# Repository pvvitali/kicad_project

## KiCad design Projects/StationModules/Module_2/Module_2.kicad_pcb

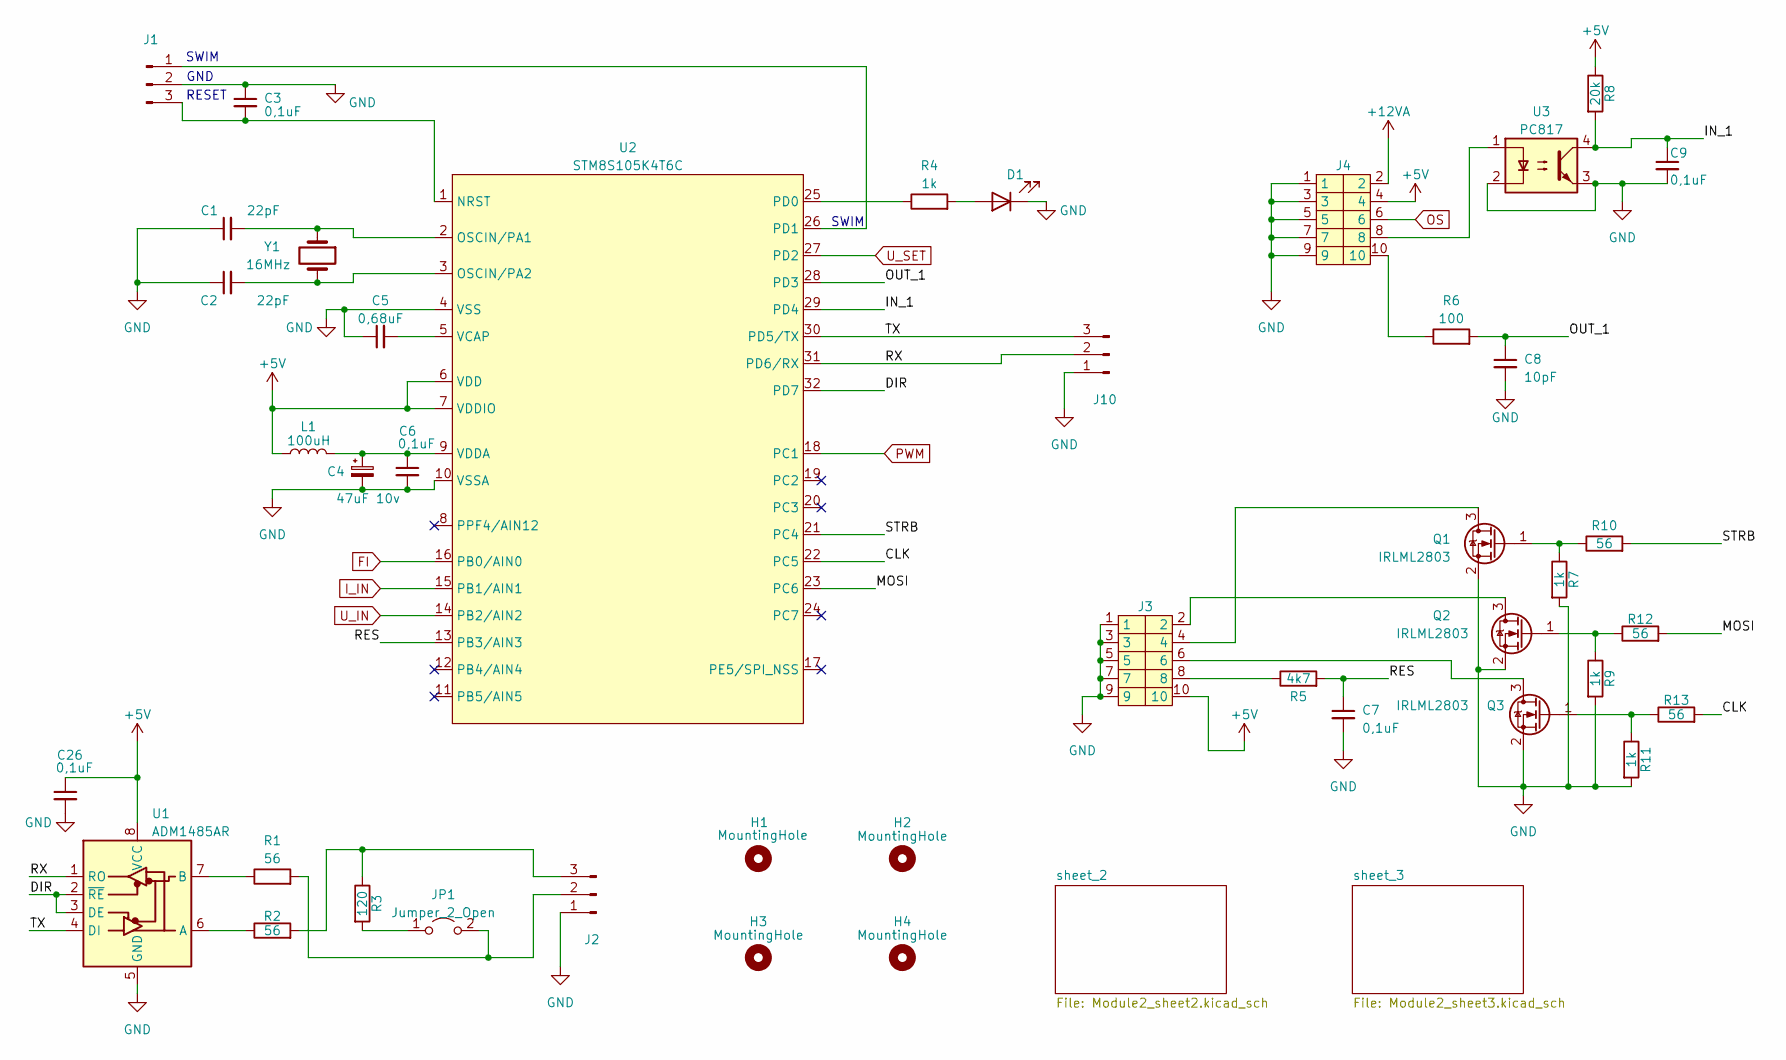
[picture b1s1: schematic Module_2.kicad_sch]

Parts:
C1, C2: 22pF; R_1206_3216Metric; MFR.Part CC1206JKNPODBN220; LCSC C577126
C3, C6, C7, C9, C26: 0,1uF; C_1206_3216Metric; MFR.Part CC1206KRX7R9BB104; LCSC C82601
C4: 47uF 10v; CP_EIA-3528-21_Kemet-B; MFR.Part T491B476K010AT; LCSC C116617
C5: 0,68uF; C_1206_3216Metric; MFR.Part CC1206KKX7R9BB684; LCSC C145012
C8: 10pF; C_1206_3216Metric; MFR.Part CC1206JRNPOBBN100; LCSC C469628
D1: LED_D3.0mm; MFR.Part TLHG4400; LCSC C3001646
H1, H2, H3, H4: MountingHole; MountingHole_3.5mm
J1: Conn_01x03_Pin; FanPinHeader_1x03_P2.54mm_Vertical; MFR.Part HB-PH3-25413PB2GOP; LCSC C49257
J2: Conn_01x03_Pin; FanPinHeader_1x03_P2.54mm_Vertical; MFR.Part 2510-3A; LCSC C29275
J3, J4: IDC-Header_2x05_P2.54mm_Vertical; MFR.Part C5665; LCSC C5665
J10: Conn_01x03_Pin; FanPinHeader_1x03_P2.54mm_Vertical; MFR.Part HB-PH3-25413PB2GOP
JP1: Jumper_2_Open; PinHeader_1x02_P2.54mm_Vertical; MFR.Part PZ254V-11-02P; LCSC C492401
L1: 100uH; L_1206_3216Metric; MFR.Part CMI321611J101KT; LCSC C128802
Q1, Q2, Q3: IRLML2803; SOT-23; MFR.Part IRLML2803TRPBF; LCSC C2590
R1, R2, R10, R12, R13: 56; R_1206_3216Metric; MFR.Part RC1206JR-0756RL; LCSC C134080
R3: 120; R_1206_3216Metric; MFR.Part RC1206JR-07100RL; LCSC C113307
R4, R7, R9, R11: 1k; R_1206_3216Metric; MFR.Part 1206W4F1001T5E; LCSC C4410
R5: 4k7; R_1206_3216Metric; MFR.Part RC1206JR-074K7L; LCSC C136458
R6: 100; R_1206_3216Metric; MFR.Part RC1206JR-07100RL; LCSC C113307
R8: 20k; R_1206_3216Metric; MFR.Part RC1206JR-0720KL; LCSC C137179
U1: ADM1485AR; SOIC-8_3.9x4.9mm_P1.27mm; MFR.Part ADM1485ARZ-REEL; LCSC C494990
U2: STM8S105K4T6C; LQFP-32_7x7mm_P0.8mm; MFR.Part STM8S105K4T6C; LCSC C8736
U3: PC817; DIP-4_W7.62mm; MFR.Part PC817X2YSZW; LCSC C2833074
Y1: 16MHz; Crystal_HC49-4H_Vertical; MFR.Part XIHCELNANF-16MHZ; LCSC C295075

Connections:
+5V: C26.1, J3.10, J4.4, L1.1, R8.1, U1.8 (VCC), U2.6 (VDD), U2.7 (VDDIO); also elsewhere on the board
+12VA: J4.2; also elsewhere on the board
/CLK: R13.2, U2.22 (PC5)
/DIR: U1.2 (~RE), U1.3 (DE), U2.32 (PD7)
/IN_1: C9.1, R8.2, U2.29 (PD4), U3.4
/MOSI: R12.2, U2.23 (PC6)
/OUT_1: C8.1, R6.2, U2.28 (PD3)
/RES: C7.1, R5.2, U2.13 (PB3/AIN3)
/RX: J10.2, U1.1 (RO), U2.31 (PD6/RX)
/STRB: R10.2, U2.21 (PC4)
/TX: J10.3, U1.4 (DI), U2.30 (PD5/TX)
FI: U2.16 (PB0/AIN0); also elsewhere on the board
GND: C1.1, C2.1, C3.1, C4.2, C5.1, C6.2, C7.2, C8.2, C9.2, C26.2, D1.2 (K), J1.2, J2.1, J3.1, J3.3, J3.5, J3.7, J3.9, J4.1, J4.3, J4.5, J4.7, J4.9, J10.1, Q1.2 (S), Q2.2 (S), Q3.2 (S), R7.2, R9.2, R11.2, U1.5 (GND), U2.4 (VSS), U2.10 (VSSA), U3.2, U3.3; also elsewhere on the board
I_IN: U2.15 (PB1/AIN1); also elsewhere on the board
unnamed: D1.1 (A), R4.2
unnamed: J1.1, U2.26 (PD1)
unnamed: C3.2, J1.3, U2.1 (NRST)
unnamed: J2.2, JP1.2 (B), R1.2
unnamed: J2.3, R2.2, R3.1
unnamed: J3.8, R5.1
unnamed: J4.8, U3.1
unnamed: J4.10, R6.1
unnamed: JP1.1 (A), R3.2
unnamed: J3.4, Q1.3 (D)
unnamed: Q1.1 (G), R7.1, R10.1
unnamed: J3.2, Q2.3 (D)
unnamed: Q2.1 (G), R9.1, R12.1
unnamed: J3.6, Q3.3 (D)
unnamed: Q3.1 (G), R11.1, R13.1
unnamed: R2.1, U1.6 (A)
unnamed: R1.1, U1.7 (B)
unnamed: C1.2, U2.2 (OSCIN/PA1), Y1.1
unnamed: C2.2, U2.3 (OSCIN/PA2), Y1.2
unnamed: R4.1, U2.25 (PD0)
unnamed: C5.2, U2.5 (VCAP)
unnamed: C4.1, C6.1, L1.2, U2.9 (VDDA)
OS: J4.6; also elsewhere on the board
PWM: U2.18 (PC1); also elsewhere on the board
U_IN: U2.14 (PB2/AIN2); also elsewhere on the board
U_SET: U2.27 (PD2); also elsewhere on the board

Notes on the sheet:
RESET
SWIM
GND

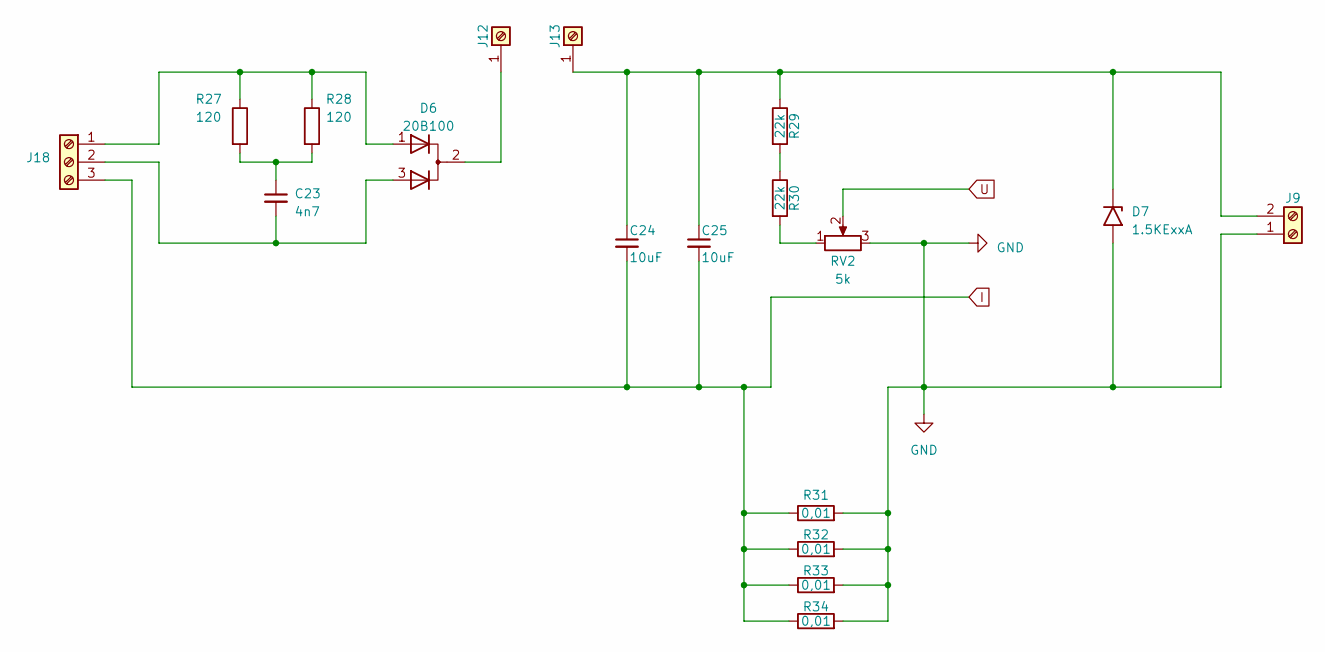
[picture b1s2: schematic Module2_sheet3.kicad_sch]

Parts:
C23: 4n7; C_Rect_L11.5mm_W5.2mm_P10.00mm_MKT; MFR.Part MPP472J2J10AJ22610; LCSC C506828
C24, C25: 10uF; C_Rect_L31.5mm_W15.0mm_P27.50mm_MKS4; MFR.Part KP106J2E2701; LCSC C5116053
D6: 20B100; TO-247-3_Horizontal_TabUp; MFR.Part MBRF20100CT; LCSC C916352
D7: 1.5KExxA; D_DO-201AE_P15.24mm_Horizontal; MFR.Part 1.5KE220A; LCSC C7464802
J9: Screw_Terminal_01x02; Klema2
J12, J13: Screw_Terminal_01x01; PinD3mm
J18: Screw_Terminal_01x03; Klema3
R27, R28: 120; R_Axial_DIN0516_L15.5mm_D5.0mm_P20.32mm_Horizontal; MFR.Part RSS3W120RJT76; LCSC C5200479
R29, R30: 22k; R_1206_3216Metric; MFR.Part AC1206JR-0722KL; LCSC C229910
R31, R32, R33, R34: 0,01; R_2816_7142Metric; MFR.Part WSL2816R0100FEH; LCSC C843884
RV2: 5k; Potentiometer_Bourns_3296W_Vertical; MFR.Part 3296W-1-502; LCSC C118907

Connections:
GND: D7.2 (A2), J9.1, R31.2, R32.2, R33.2, R34.2, RV2.3; also elsewhere on the board
I: C24.2, C25.2, J18.3, R31.1, R32.1, R33.1, R34.1; also elsewhere on the board
unnamed: C23.1, R27.2, R28.2
unnamed: D6.2 (A), J12.1
unnamed: C24.1, C25.1, D7.1 (A1), J9.2, J13.1, R29.1
unnamed: D6.1 (K), J18.1, R27.1, R28.1
unnamed: C23.2, D6.3 (K), J18.2
unnamed: R29.2, R30.1
unnamed: R30.2, RV2.1
U: RV2.2; also elsewhere on the board

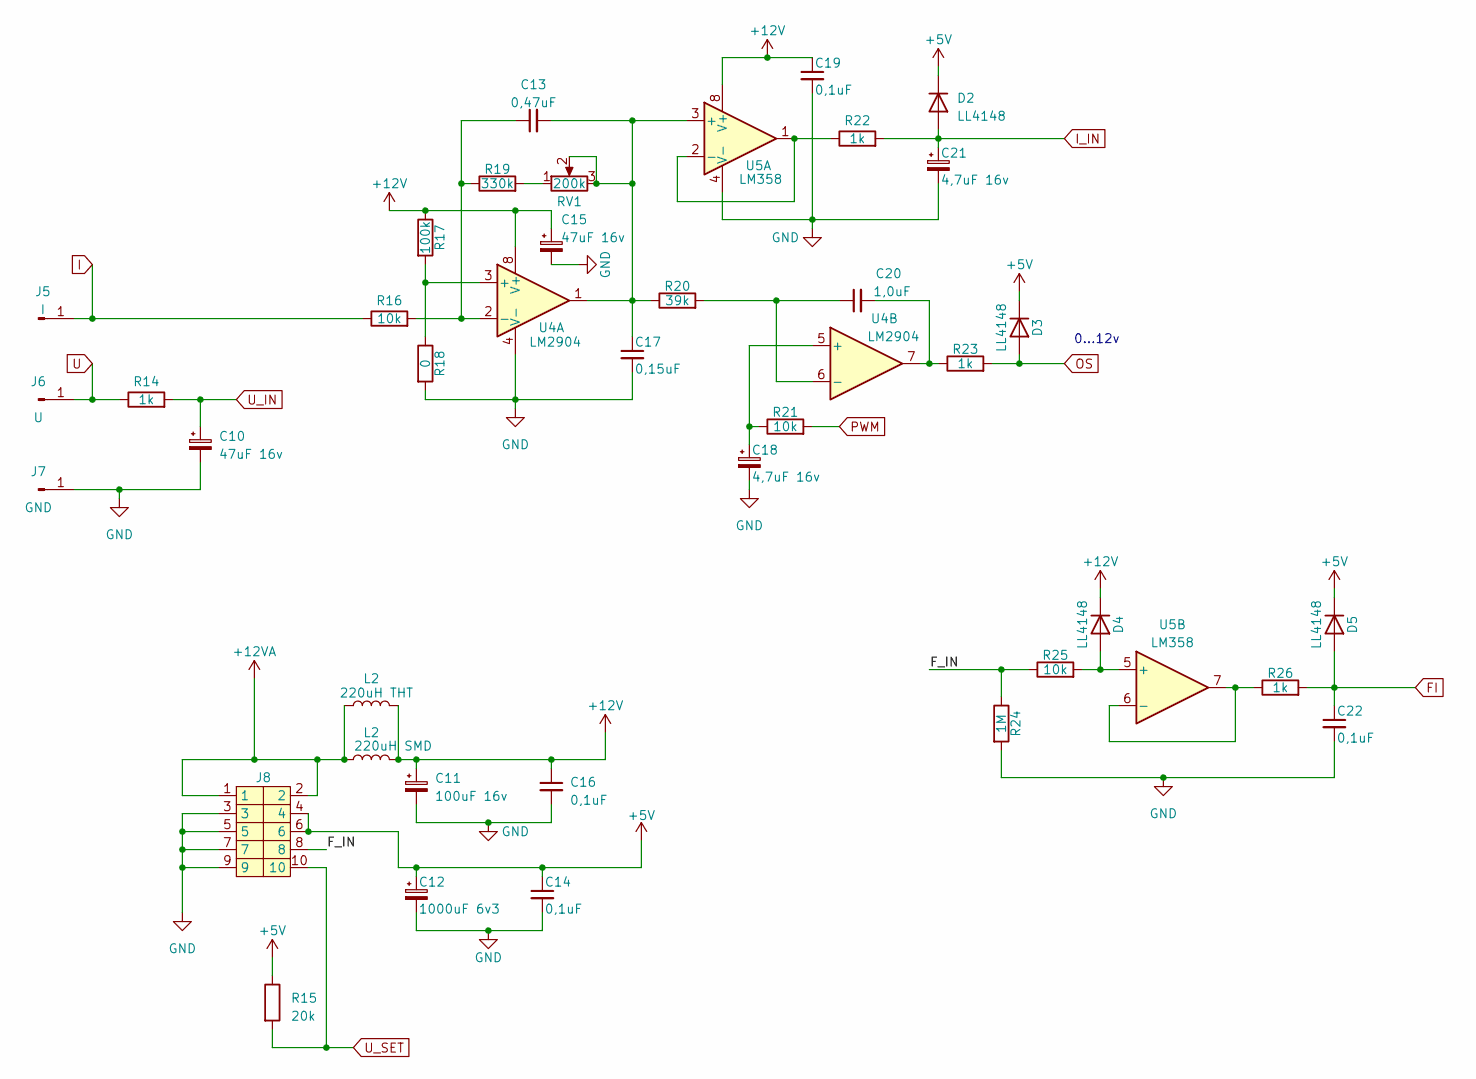
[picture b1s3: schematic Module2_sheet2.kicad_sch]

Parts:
C10, C15: 47uF 16v; CP_Radial_D8.0mm_P5.00mm; MFR.Part KM470M016C110A; LCSC C59402
C11: 100uF 16v; CP_Radial_D8.0mm_P5.00mm; MFR.Part 16YXJ100M5X11; LCSC C108735
C12: 1000uF 6v3; CP_Radial_D8.0mm_P5.00mm; MFR.Part 6.3YXJ1000M8X11.5; LCSC C694350
C13: 0,47uF; C_1206_3216Metric; MFR.Part CC1206KKX7R9BB474; LCSC C277483
C14, C16, C19, C22: 0,1uF; C_1206_3216Metric; MFR.Part CC1206KRX7R9BB104; LCSC C82601
C17: 0,15uF; C_1206_3216Metric; MFR.Part CC1206JKX7R9BB154; LCSC C2171172
C18, C21: 4,7uF 16v; CP_Radial_D8.0mm_P5.00mm; MFR.Part 50PX4R7MEFC5X11; LCSC C122950
C20: 1,0uF; C_1206_3216Metric; MFR.Part CC1206KKX7R9BB105; LCSC C107185
D2, D3, D4, D5: LL4148; D_MiniMELF; MFR.Part LL4148; LCSC C2891733
J5: I; Pin_D1.0mm_L10.0mm
J6: U; Pin_D1.0mm_L10.0mm
J7: GND; Pin_D1.0mm_L10.0mm
J8: IDC-Header_2x05_P2.54mm_Vertical; MFR.Part C5665; LCSC C5665
L2: 220uH THT; L_Axial_L7.0mm_D3.3mm_P10.16mm_Horizontal_Fastron_MICC
R14, R22, R23, R26: 1k; R_1206_3216Metric; MFR.Part 1206W4F1001T5E; LCSC C4410
R15: 20k; R_1206_3216Metric; MFR.Part RC1206JR-0720KL; LCSC C137179
R16, R21, R25: 10k; R_1206_3216Metric; MFR.Part RC1206JR-0710KL; LCSC C136460
R17: 100k; R_1206_3216Metric; MFR.Part RC1206JR-07100KL; LCSC C136470
R18: 0; R_1206_3216Metric; MFR.Part 1206W4F0000T5E; LCSC C17888
R19: 330k; R_1206_3216Metric; MFR.Part 1206W4F3303T5E; LCSC C17929
R20: 39k; R_1206_3216Metric; MFR.Part FRC1206J393 TS; LCSC C2907491
R24: 1M; R_1206_3216Metric; MFR.Part RC1206JR-071ML; LCSC C148194
RV1: 200k; Potentiometer_Bourns_3296W_Vertical; MFR.Part 3296W-1-204LF; LCSC C58354
U4: LM2904; SO-8_3.9x4.9mm_P1.27mm; MFR.Part LM2904; LCSC C2941725
U5: LM358; SO-8_3.9x4.9mm_P1.27mm; MFR.Part LM358D; LCSC C2683482

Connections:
+5V: C12.1, C14.1, D2.1 (K), D3.1 (K), D5.1 (K), J8.4, J8.6, R15.1; also elsewhere on the board
+12V: C11.1, C15.1, C16.1, C19.1, D4.1 (K), L2.2, R17.1, U4.8 (V+), U5.8 (V+); also elsewhere on the board
+12VA: J8.1, J8.2, L2.1; also elsewhere on the board
/sheet_2/F_IN: J8.8, R24.1, R25.1
FI: C22.1, D5.2 (A), R26.2; also elsewhere on the board
GND: C10.2, C11.2, C12.2, C14.2, C15.2, C16.2, C17.2, C18.2, C19.2, C21.2, C22.2, J7.1, J8.3, J8.5, J8.7, J8.9, R18.2, R24.2, U4.4 (V-), U5.4 (V-); also elsewhere on the board
I: J5.1, R16.1; also elsewhere on the board
I_IN: C21.1, D2.2 (A), R22.2; also elsewhere on the board
unnamed: C20.2, R23.1, U4.7
unnamed: D4.2 (A), R25.2, U5.5 (+)
unnamed: R19.2, RV1.1
unnamed: R17.2, R18.1, U4.3 (+)
unnamed: C13.1, R16.2, R19.1, U4.2 (-)
unnamed: C18.1, R21.1, U4.5 (+)
unnamed: C20.1, R20.2, U4.6 (-)
unnamed: C13.2, C17.1, R20.1, RV1.2, RV1.3, U4.1, U5.3 (+)
unnamed: R22.1, U5.1, U5.2 (-)
unnamed: R26.1, U5.6 (-), U5.7
OS: D3.2 (A), R23.2; also elsewhere on the board
PWM: R21.2; also elsewhere on the board
U: J6.1, R14.1; also elsewhere on the board
U_IN: C10.1, R14.2; also elsewhere on the board
U_SET: J8.10, R15.2; also elsewhere on the board

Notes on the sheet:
0...12v

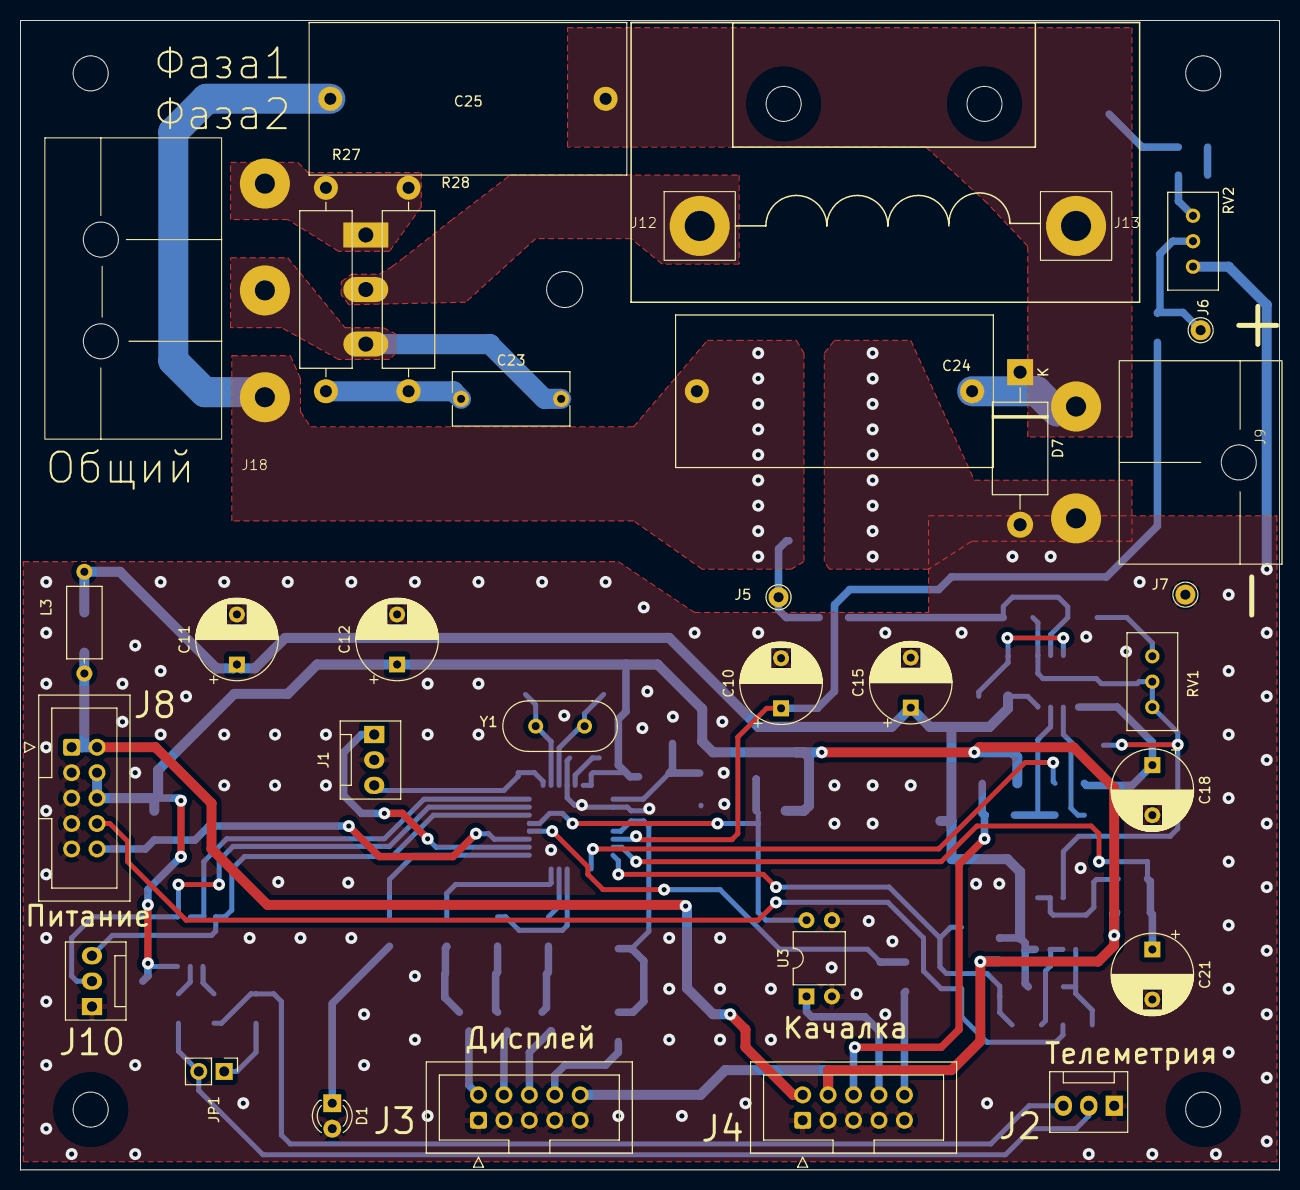
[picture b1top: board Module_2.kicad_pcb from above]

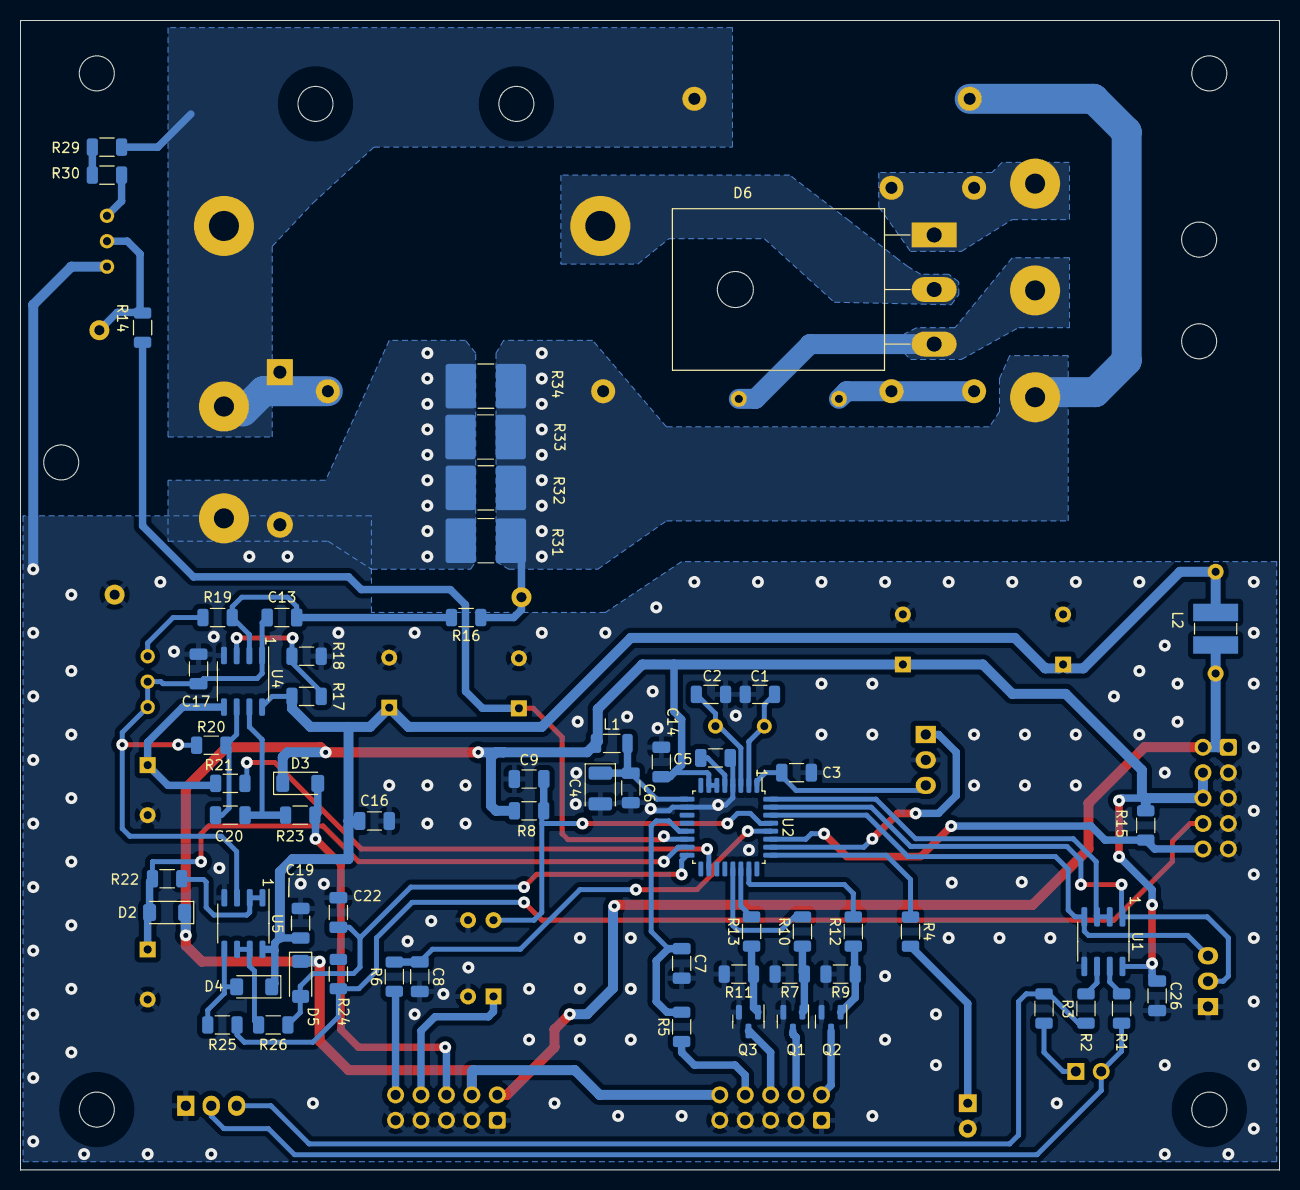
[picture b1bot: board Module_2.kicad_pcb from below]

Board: 2 copper layers, 125.8 x 114.8 mm, 101 parts (63 on the bottom side), 61 nets.

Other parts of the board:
H2#2, H2#3: MountingHole; MountingHole_3.5mm
L3: 220uH THT; L_Axial_L7.0mm_D3.3mm_P10.16mm_Horizontal_Fastron_MICC

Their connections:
+12V: L3.2; also elsewhere on the board
+12VA: L3.1; also elsewhere on the board

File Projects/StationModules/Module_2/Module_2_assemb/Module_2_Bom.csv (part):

"Reference","Value","Footprint","Description","LCSC","MFR.Part","Mounting","Qty"
"C1, C2","22pF","Resistor_SMD:R_1206_3216Metric","2kV 22pF NP0 ±5% 1206 Multilayer Ceramic Capacitors MLCC - SMD/SMT ROHS","C577126","CC1206JKNPODBN220","Yes","2"
"C3, C6, C7, C9, C14, C16, C19, C22, C26","0,1uF","Capacitor_SMD:C_1206_3216Metric","50V 100nF X7R ±10% 1206 Multilayer Ceramic Capacitors MLCC - SMD/SMT ROHS","C82601","CC1206KRX7R9BB104","Yes","9"
"C4","47uF 10v","Capacitor_Tantalum_SMD:CP_EIA-3528-21_Kemet-B","47uF 10V 1Ω@100kHz ±10% CASE-B-3528 Tantalum Capacitors ROHS","C116617","T491B476K010AT","Yes","1"
"C5","0,68uF","Capacitor_SMD:C_1206_3216Metric","50V 680nF X7R ±10% 1206 Multilayer Ceramic Capacitors MLCC - SMD/SMT ROHS","C145012","CC1206KKX7R9BB684","Yes","1"
"C8","10pF","Capacitor_SMD:C_1206_3216Metric","500V 10pF NP0 ±5% 1206 Multilayer Ceramic Capacitors MLCC - SMD/SMT ROHS","C469628","CC1206JRNPOBBN100","Yes","1"
"C10, C15","47uF 16v","Capacitor_THT:CP_Radial_D8.0mm_P5.00mm","47uF 16V ±20% 73mA@120Hz Plugin,D5xL7mm Aluminum Electrolytic Capacitors - Leaded ROHS","C59402","KM470M016C110A","Yes","2"
"C11","100uF 16v","Capacitor_THT:CP_Radial_D8.0mm_P5.00mm","100uF 16V 400mΩ@100kHz ±20% 250mA@100kHz Plugin,D5xL11mm Aluminum Electrolytic Capacitors - Leaded ROHS","C108735","16YXJ100M5X11","Yes","1"
"C12","1000uF 6v3","Capacitor_THT:CP_Radial_D8.0mm_P5.00mm","1000uF 6.3V ±20% Plugin,D8xL11.5mm Aluminum Electrolytic Capacitors - Leaded ROHS","C694350","6.3YXJ1000M8X11.5","Yes","1"
"C13","0,47uF","Capacitor_SMD:C_1206_3216Metric","50V 470nF X7R ±10% 1206 Multilayer Ceramic Capacitors MLCC - SMD/SMT ROHS","C277483","CC1206KKX7R9BB474","Yes","1"
"C17","0,15uF","Capacitor_SMD:C_1206_3216Metric","50V 150nF X7R ±5% 1206 Multilayer Ceramic Capacitors MLCC - SMD/SMT ROHS","C2171172","CC1206JKX7R9BB154","Yes","1"
"C18, C21","4,7uF 16v","Capacitor_THT:CP_Radial_D8.0mm_P5.00mm","4.7uF 50V ±20% Plugin,D5xL11mm Aluminum Electrolytic Capacitors - Leaded ROHS","C122950","50PX4R7MEFC5X11","Yes","2"
"C20","1,0uF","Capacitor_SMD:C_1206_3216Metric","50V 1uF X7R ±10% 1206 Multilayer Ceramic Capacitors MLCC - SMD/SMT ROHS","C107185","CC1206KKX7R9BB105","Yes","1"
"C23","4n7","Capacitor_THT:C_Rect_L11.5mm_W5.2mm_P10.00mm_MKT","4.7nF ±5% 630V Plugin,P=10mm Polypropylene Film Capacitors (CBB) ROHS","C506828","MPP472J2J10AJ22610","Yes","1"
"C24, C25","10uF","Capacitor_THT:C_Rect_L31.5mm_W15.0mm_P27.50mm_MKS4","10uF ±5% 250V Plugin,P=27.5mm Polypropylene Film Capacitors (CBB) ROHS","C5116053","KP106J2E2701","Yes","2"
"D1","","LED_THT:LED_D3.0mm","green Plugin,D=3.2mm Light Emitting Diodes (LED) ROHS","C3001646","TLHG4400","Yes","1"
"D2-D5","LL4148","Diode_SMD:D_MiniMELF","75V 500mW 1V@10mA 4ns 150mA LL-34 Switching Diode ROHS","C2891733","LL4148","Yes","4"
"D6","20B100","Package_TO_SOT_THT:TO-247-3_Horizontal_TabUp","Dual Common Cathode 830mV@20A 100V 10A TO-220F-3 Schottky Barrier Diodes (SBD) ROHS","C916352","MBRF20100CT","No","1"
"H1-H4","MountingHole","MountingHole:MountingHole_3.5mm","","","","No","4"
"J1, J2, J10","Conn_01x03_Pin","Connector:FanPinHeader_1x03_P2.54mm_Vertical","Gold 250V 3A Straight Square Pins 2.54mm 3P 260℃ 6mm -40℃~+105℃ 3mm 2.54mm Brass Black Plugin 2.54mm 1x3P Plugin,P=2.54mm Pin Headers ROHS","C49257","HB-PH3-25413PB2GOP","Yes","3"
"J3, J4, J8","","Connector_IDC:IDC-Header_2x05_P2.54mm_Vertical","2.54mm Straight 2x5P 5 Push - Pull 2.54mm 2 Plugin,P=2.54mm IDC Connectors ROHS","C5665","C5665","Yes","3"
"J5","I","Connector_Pin:Pin_D1.0mm_L10.0mm","","","","No","1"
"J6","U","Connector_Pin:Pin_D1.0mm_L10.0mm","","","","No","1"
"J7","GND","Connector_Pin:Pin_D1.0mm_L10.0mm","","","","No","1"
"J9","Screw_Terminal_01x02","Z_connectors:Klema2","","","","No","1"
"J12, J13","Screw_Terminal_01x01","Z_pin:PinD3mm","","","","No","2"
"J18","Screw_Terminal_01x03","Z_connectors:Klema3","","","","No","1"
"JP1","Jumper_2_Open","Connector_PinHeader_2.54mm:PinHeader_1x02_P2.54mm_Vertical","3A Straight 2.54mm -65℃~+125℃ 2.54mm 双排 Black Phosphor bronze 2.54mm Plugin,P=2.54mm Pin Headers ROHS","C492401","PZ254V-11-02P","Yes","1"
"L1","100uH","Inductor_SMD:L_1206_3216Metric","100uH ±10% 1206 Inductors (SMD) ROHS","C128802","CMI321611J101KT","Yes","1"
"L2","220uH  SMD","Inductor_SMD:L_Ferrocore_DLG-0403","360mA 220uH ±20% SMD,4.5x4x3.2mm Power Inductors ROHS","C492283","CD43YP0403-221M","Yes","1"
"L3","220uH THT","Inductor_THT:L_Axial_L7.0mm_D3.3mm_P10.16mm_Horizontal_Fastron_MICC","","","","No","1"
"Q1-Q3","IRLML2803","Package_TO_SOT_SMD:SOT-23","30V 1.2A 540mW 250mΩ@10V,910mA N Channel SOT-23 MOSFETs ROHS","C2590","IRLML2803TRPBF","Yes","3"
"R1, R2, R10, R12, R13","56","Resistor_SMD:R_1206_3216Metric","250mW Thick Film Resistors ±100ppm/℃ ±5% 56Ω 1206 Chip Resistor - Surface Mount ROHS","C134080","RC1206JR-0756RL","Yes","5"
"R3","120","Resistor_SMD:R_1206_3216Metric","250mW Thick Film Resistors ±100ppm/℃ ±5% 100Ω 1206 Chip Resistor - Surface Mount ROHS","C113307","RC1206JR-07100RL","Yes","1"
"R4, R7, R9, R11, R14, R22, R23, R26","1k","Resistor_SMD:R_1206_3216Metric","250mW Thick Film Resistors ±100ppm/℃ ±5% 1kΩ 1206 Chip Resistor - Surface Mount ROHS","C112223","RC1206JR-071KL","Yes","8"
"R5","4k7","Resistor_SMD:R_1206_3216Metric","250mW Thick Film Resistors ±100ppm/℃ ±5% 4.7kΩ 1206 Chip Resistor - Surface Mount ROHS","C136458","RC1206JR-074K7L","Yes","1"
"R6","100","Resistor_SMD:R_1206_3216Metric","250mW Thick Film Resistors ±100ppm/℃ ±5% 100Ω 1206 Chip Resistor - Surface Mount ROHS","C113307","RC1206JR-07100RL","Yes","1"
"R8, R15","20k","Resistor_SMD:R_1206_3216Metric","250mW Thick Film Resistors ±100ppm/℃ ±5% 20kΩ 1206 Chip Resistor - Surface Mount ROHS","C137179","RC1206JR-0720KL","Yes","2"
"R16, R21, R25","10k","Resistor_SMD:R_1206_3216Metric","250mW Thick Film Resistors ±100ppm/℃ ±5% 10kΩ 1206 Chip Resistor - Surface Mount ROHS","C136460","RC1206JR-0710KL","Yes","3"
"R17","100k","Resistor_SMD:R_1206_3216Metric","250mW Thick Film Resistors ±100ppm/℃ ±5% 100kΩ 1206 Chip Resistor - Surface Mount ROHS","C136470","RC1206JR-07100KL","No","1"
"R18","0","Resistor_SMD:R_1206_3216Metric","250mW Thick Film Resistors ±800ppm/℃ ±1% 0Ω 1206 Chip Resistor - Surface Mount ROHS","C17888","1206W4F0000T5E","Yes","1"
"R19","330k","Resistor_SMD:R_1206_3216Metric","250mW Thick Film Resistors ±100ppm/℃ ±1% 330kΩ 1206 Chip Resistor - Surface Mount ROHS","C17929","1206W4F3303T5E","Yes","1"
"R20","39k","Resistor_SMD:R_1206_3216Metric","250mW Thick Film Resistors ±100ppm/℃ ±5% 39kΩ 1206 Chip Resistor - Surface Mount ROHS","C2907491","FRC1206J393 TS","Yes","1"
"R24","1M","Resistor_SMD:R_1206_3216Metric","250mW Thick Film Resistors ±100ppm/℃ ±5% 1MΩ 1206 Chip Resistor - Surface Mount ROHS","C148194","RC1206JR-071ML","Yes","1"
"R27, R28","120","Resistor_THT:R_Axial_DIN0516_L15.5mm_D5.0mm_P20.32mm_Horizontal","120Ω 3W ±5% - Through Hole Resistors ROHS","C5200479","RSS3W120RJT76","Yes","2"
"R29, R30","22k","Resistor_SMD:R_1206_3216Metric","250mW Thick Film Resistors ±100ppm/℃ ±5% 22kΩ 1206 Chip Resistor - Surface Mount ROHS","C229910","AC1206JR-0722KL","Yes","2"
"R31-R34","0,01","Resistor_SMD:R_2816_7142Metric","2W ±75ppm/℃ ±1% 10mΩ 2816 Chip Resistor - Surface Mount ROHS","C843884","WSL2816R0100FEH","Yes","4"
"RV1","200k","Potentiometer_THT:Potentiometer_Bourns_3296W_Vertical","±10% ±100ppm/℃ 500mW 200kΩ Plugin Variable Resistors/Potentiometers ROHS","C58354","3296W-1-204LF","Yes","1"
"RV2","5k","Potentiometer_THT:Potentiometer_Bourns_3296W_Vertical","±10% 5kΩ Plugin Variable Resistors/Potentiometers ROHS","C118907","3296W-1-502","Yes","1"
"U1","ADM1485AR","Package_SO:SOIC-8_3.9x4.9mm_P1.27mm","transceiver 30Mbps 1/1 SOP-8 RS-485/RS-422 ICs ROHS","C494990","ADM1485ARZ-REEL","Yes","1"
"U2","STM8S105K4T6C","Package_QFP:LQFP-32_7x7mm_P0.8mm","25 STM8 16MHz 2.95V~5.5V 2KB FLASH 16KB LQFP-32(7x7) Microcontroller Units (MCUs/MPUs/SOCs) ROHS","C8736","STM8S105K4T6C","Yes","1"
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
